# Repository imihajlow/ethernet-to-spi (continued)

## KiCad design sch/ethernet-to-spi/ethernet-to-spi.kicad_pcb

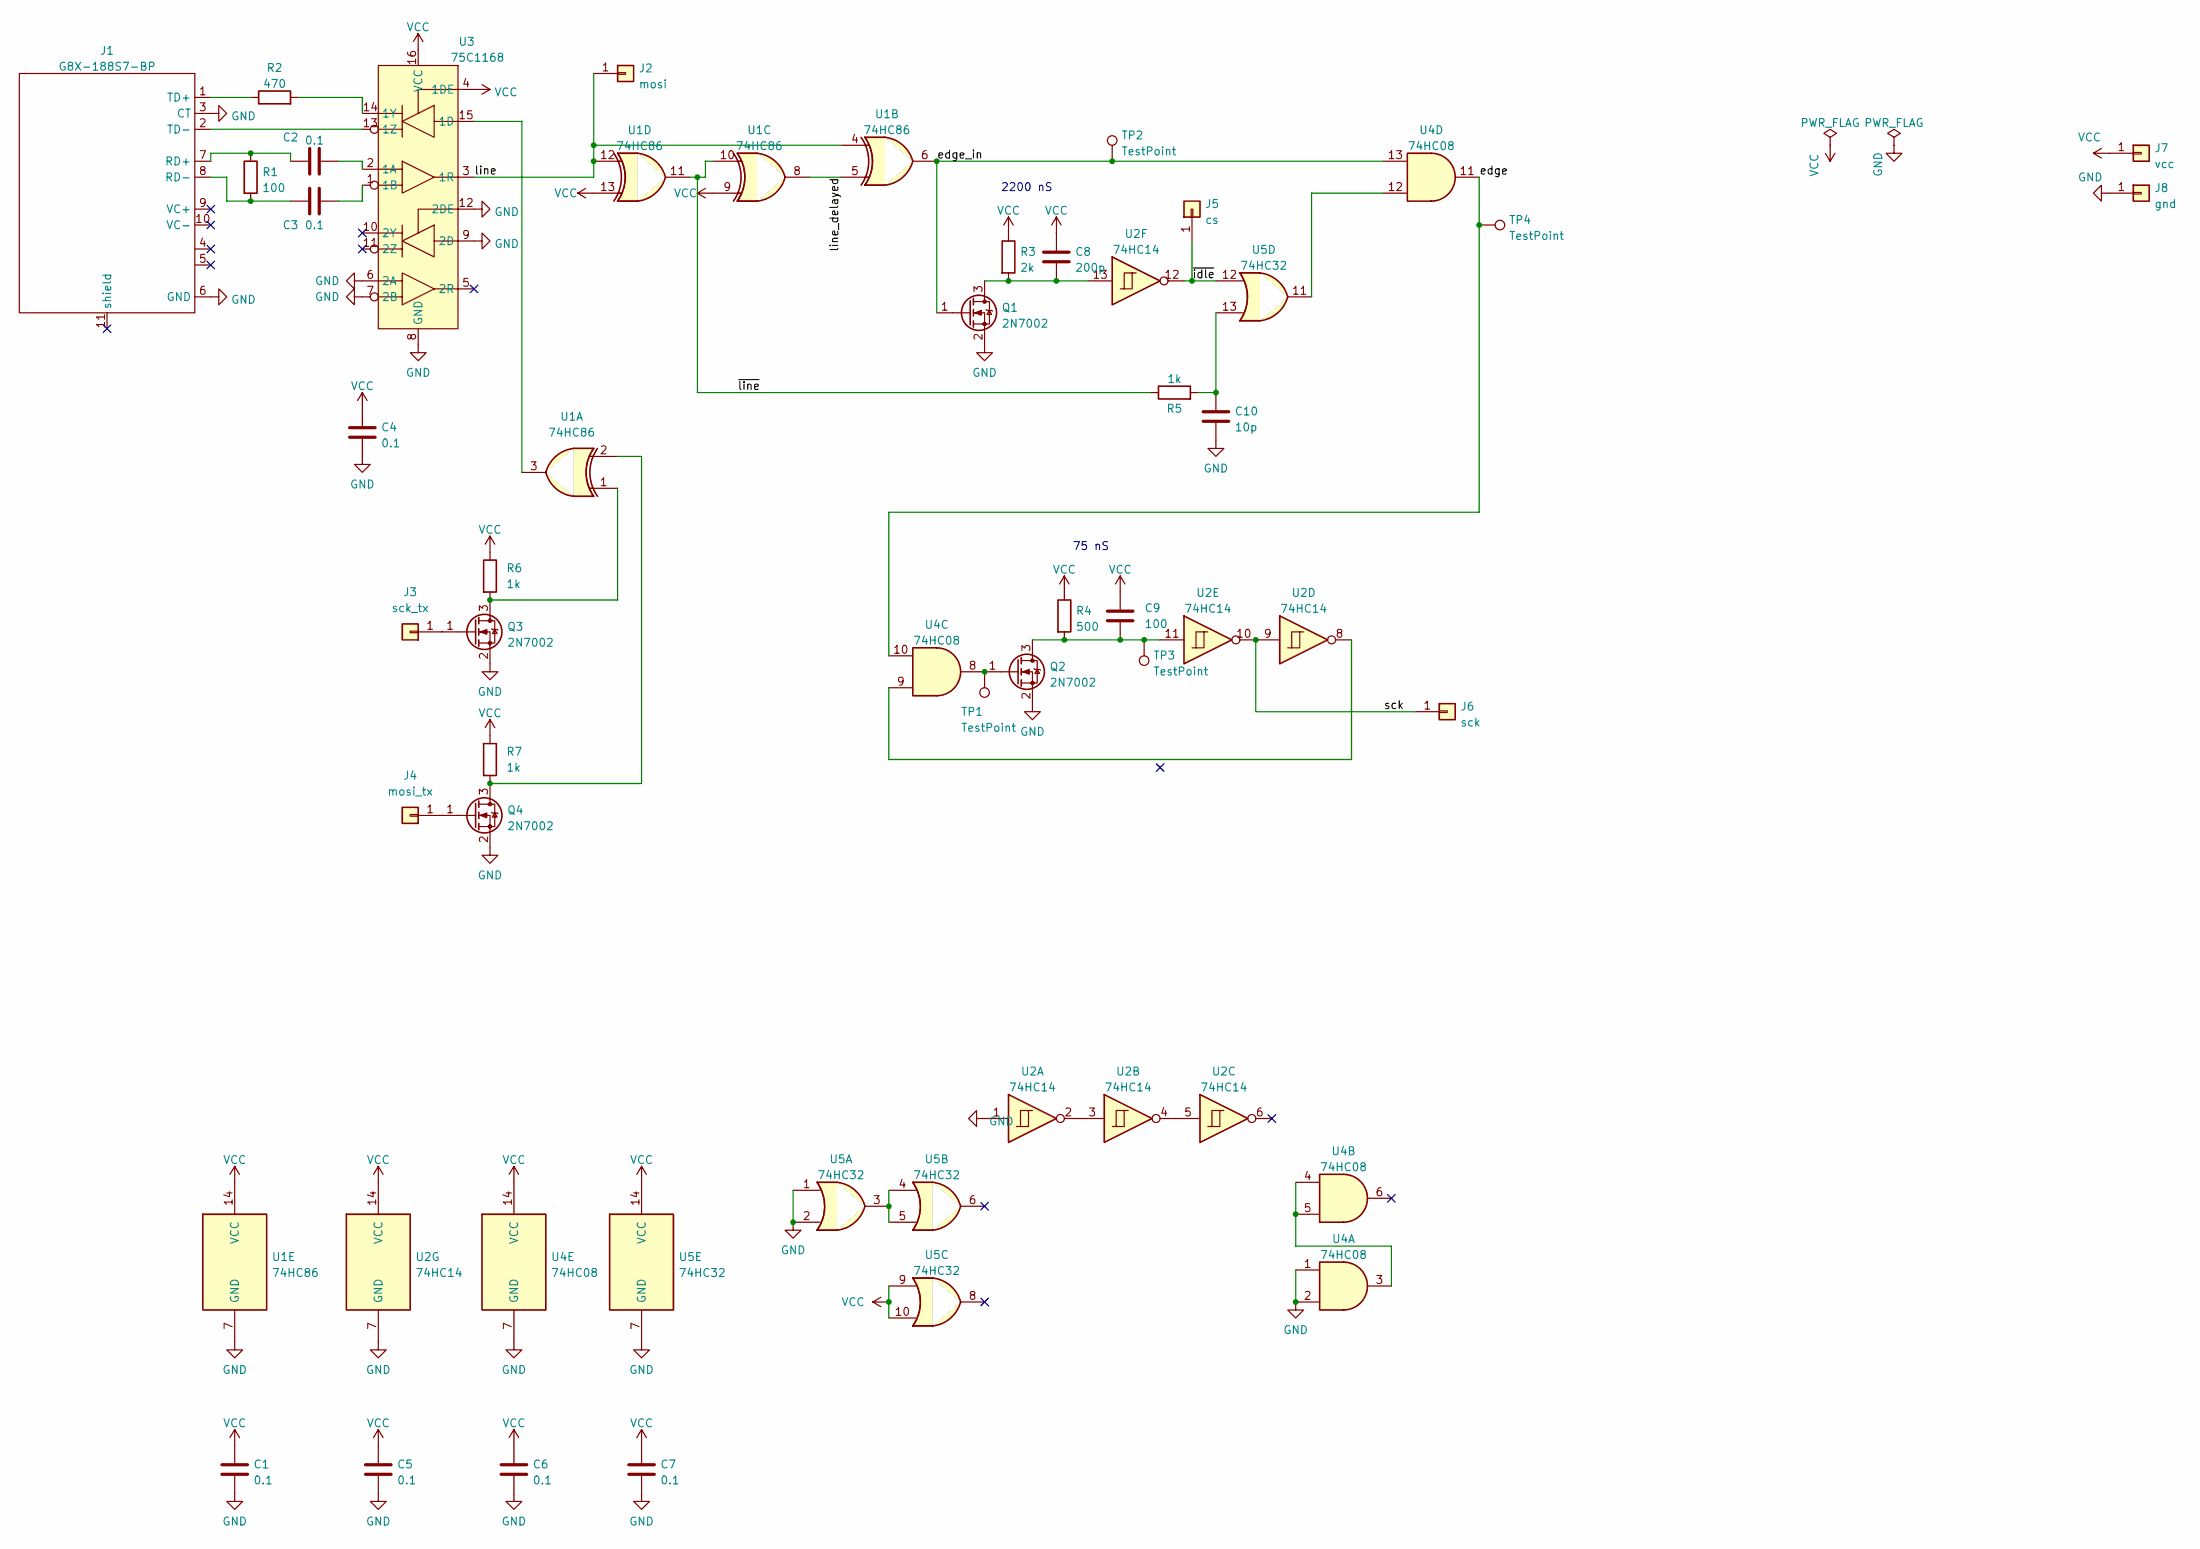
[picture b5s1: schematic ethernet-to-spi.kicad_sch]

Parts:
C1, C2, C3, C4, C5, C6, C7: 0.1; C_0805_2012Metric
C8: 200p; C_0805_2012Metric
C9: 100; C_0805_2012Metric
C10: 10p; C_0805_2012Metric
J1: G8X-188S7-BP
J2: mosi; SolderWire-0.25sqmm_1x01_D0.65mm_OD2mm_Relief
J3: sck_tx; SolderWire-0.25sqmm_1x01_D0.65mm_OD2mm_Relief
J4: mosi_tx; SolderWire-0.25sqmm_1x01_D0.65mm_OD2mm_Relief
J5: cs; SolderWire-0.25sqmm_1x01_D0.65mm_OD2mm_Relief
J6: sck; SolderWire-0.25sqmm_1x01_D0.65mm_OD2mm_Relief
J7: vcc; SolderWire-0.25sqmm_1x01_D0.65mm_OD2mm_Relief
J8: gnd; SolderWire-0.25sqmm_1x01_D0.65mm_OD2mm_Relief
Q1, Q2, Q3, Q4: 2N7002; SOT-23
R1: 100; R_0805_2012Metric
R2: 470; R_0805_2012Metric
R3: 2k; R_0805_2012Metric
R4: 500; R_0805_2012Metric
R5: 1k; R_Axial_DIN0207_L6.3mm_D2.5mm_P15.24mm_Horizontal
R6, R7: 1k; R_0805_2012Metric
TP1, TP2, TP3, TP4: TestPoint; TestPoint_Pad_D3.0mm
U1: 74HC86; SOIC-14_3.9x8.7mm_P1.27mm
U2: 74HC14; SOIC-14_3.9x8.7mm_P1.27mm
U3: 75C1168; DIP-16_W7.62mm
U4: 74HC08; SOIC-14_3.9x8.7mm_P1.27mm
U5: 74HC32; SOIC-14_3.9x8.7mm_P1.27mm

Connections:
/edge: TP4.1, U4.10, U4.11
/edge_in: Q1.1 (G), TP2.1, U1.6, U4.13
/line: J2.1, U1.4, U1.12, U3.3 (1R)
/line_delayed: U1.5, U1.8
/sck: J6.1, U2.9, U2.10
/~idle: J5.1, U2.12, U5.12
/~line: R5.1, U1.10, U1.11
GND: C1.2, C4.2, C5.2, C6.2, C7.2, C10.2, J1.3 (CT), J1.6 (GND), J8.1, Q1.2 (S), Q2.2 (S), Q3.2 (S), Q4.2 (S), U1.7 (GND), U2.1, U2.7 (GND), U3.6 (2A), U3.7 (2B), U3.8 (GND), U3.9 (2D), U3.12 (2DE), U4.1, U4.2, U4.7 (GND), U5.1, U5.2, U5.7 (GND)
unnamed: C2.1, J1.7 (RD+), R1.1
unnamed: C2.2, U3.2 (1A)
unnamed: C3.1, J1.8 (RD-), R1.2
unnamed: C3.2, U3.1 (1B)
unnamed: C8.2, Q1.3 (D), R3.2, U2.13
unnamed: C9.2, Q2.3 (D), R4.2, TP3.1, U2.11
unnamed: J1.1 (TD+), R2.1
unnamed: J1.2 (TD-), U3.13 (1Z)
unnamed: J3.1, Q3.1 (G)
unnamed: J4.1, Q4.1 (G)
unnamed: Q2.1 (G), TP1.1, U4.8
unnamed: R2.2, U3.14 (1Y)
unnamed: C10.1, R5.2, U5.13
unnamed: Q3.3 (D), R6.2, U1.1
unnamed: Q4.3 (D), R7.2, U1.2
unnamed: U1.3, U3.15 (1D)
unnamed: U2.2, U2.3
unnamed: U2.4, U2.5
unnamed: U2.8, U4.9
unnamed: U4.3, U4.4, U4.5
unnamed: U5.3, U5.4, U5.5
unnamed: U4.12, U5.11
VCC: C1.1, C4.1, C5.1, C6.1, C7.1, C8.1, C9.1, J7.1, R3.1, R4.1, R6.1, R7.1, U1.9, U1.13, U1.14 (VCC), U2.14 (VCC), U3.4 (1DE), U3.16 (VCC), U4.14 (VCC), U5.9, U5.10, U5.14 (VCC)

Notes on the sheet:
2200 nS
75 nS

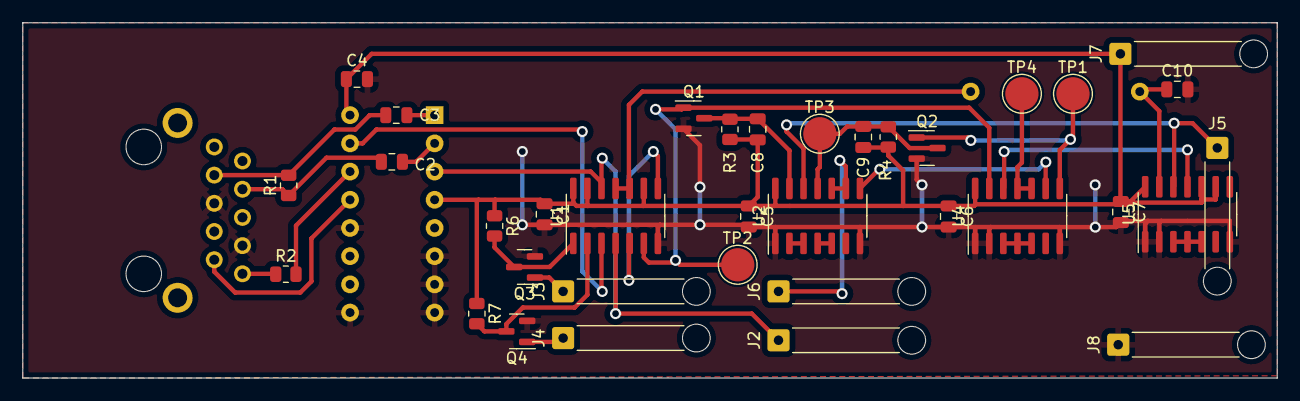
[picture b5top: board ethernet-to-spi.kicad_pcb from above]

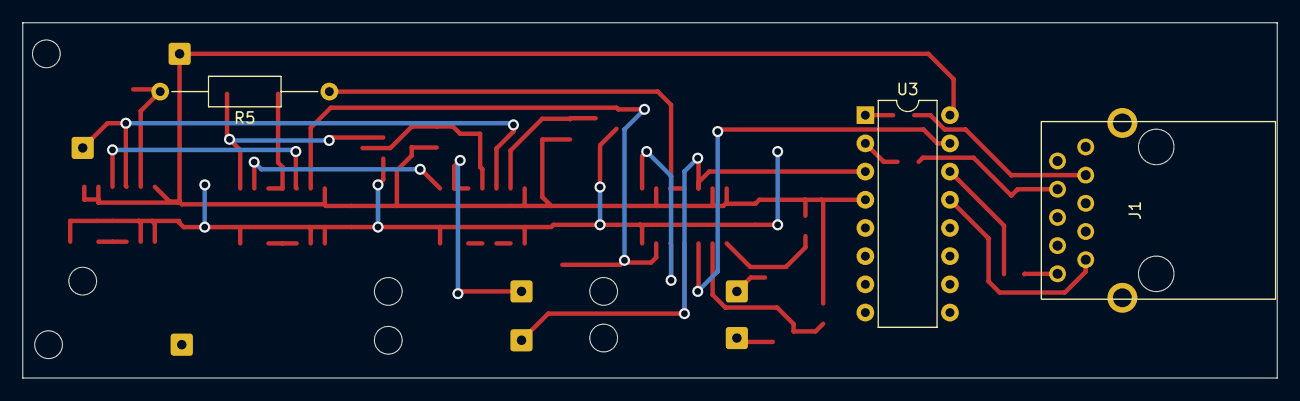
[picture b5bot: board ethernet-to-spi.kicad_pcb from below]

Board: 2 copper layers, 113.0 x 32.0 mm, 38 parts (3 on the bottom side), 31 nets.

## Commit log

2022-09-01 Waveforms
2022-09-04 SPI to UART
2022-09-04 Reset SPI after each transfer
2022-09-04 Add 74xx models
2022-09-07 Model and schematics of a receiver
2022-09-07 Change SPI bit order and CS polarity
2022-09-07 Add Readme
2022-09-07 Fix italics
2022-09-07 Fix links
2022-09-07 Fix image name
2022-09-08 Fix first edge filter circuit, create PCB
2022-09-09 Add level shifters for inputs
2022-09-11 Update capacitor value for 75 nS delay
2022-09-11 Produce NLP
2022-09-11 Gerber files
2022-09-14 Transmit a packet
2022-09-18 Receiver WIP
2022-09-18 NLP generator
2022-09-18 Transmitter
2022-09-19 NLP generator board
2022-09-19 Device for smoltcp
2022-09-20 defmt
2022-09-20 ping works
2022-09-21 Pad frames to 64 bytes
2022-10-04 HTTP Server hello world
2022-10-12 Server WIP
2022-10-19 Porting to STM32F401 WIP
2022-11-06 Byte synchronization module + STM32F401 program (works partially)
2022-11-08 Receiver: try flipping first bit, recover on false edges
2022-11-09 Multiple receive buffers
2022-11-09 Re-enable server
2022-11-13 New transmitter board
2022-11-13 Add index.html
2022-11-13 Fix NLP polarity
2022-11-15 Shield schematic
2022-11-17 Shield board
2022-11-17 Shield board production files
2022-11-25 Fix error in board
2022-11-27 Trying TLS
2022-11-29 Telegram bot: get last update
2022-11-30 Telegram echo bot
2022-12-03 Async select message and button event
2022-12-05 Echo a message and notify of button press
2022-12-05 Unescape strings received from JSON
2022-12-05 Rename tls_task -> bot_task
2022-12-05 RM index.html
2022-12-05 Construct RNGs inside bot task
2022-12-05 Unescape high codepoints
2022-12-05 Apply rustfmt
2022-12-06 Add license
2022-12-06 Change README
